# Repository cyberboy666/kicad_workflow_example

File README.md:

# kicad_workflow_example
an example kicad project to experiment with automated workflows

## goals

on every git _push_:
- check the schematic and pcb tester for problems (dont block just alert if there is something)

on every git _release_:
- run checkers...
- export schematic pdf
- export gerber files (lastest.zip format ?)
- export the bom's (full, tayda, mouser ibom)

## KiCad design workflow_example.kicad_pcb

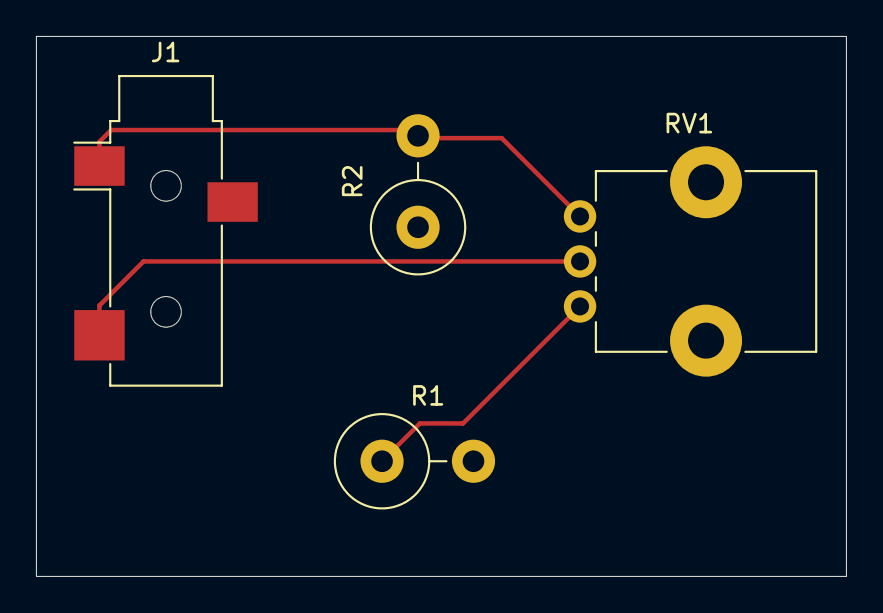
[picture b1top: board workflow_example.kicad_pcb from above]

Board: 2 copper layers, 45.0 x 30.0 mm, 4 parts (0 on the bottom side), 4 nets.

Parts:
J1: AudioJack2; Jack_3.5mm_CUI_SJ-3523-SMT_Horizontal
R1, R2: R; R_Axial_DIN0516_L15.5mm_D5.0mm_P5.08mm_Vertical
RV1: R_POT; Potentiometer_Alps_RK09K_Single_Vertical

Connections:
GND: J1.S, R2.1
unnamed: J1.T, RV1.2
unnamed: R1.1, RV1.1
unnamed: R2.2, RV1.3

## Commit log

2020-11-04 test commit
2020-11-04 change
2020-11-04 refolder
2020-11-04 add pcb
2020-11-04 example change
2020-11-04 update circuit
2020-11-04 Add changes
2020-11-04 broken schematic
2020-11-04 fix schematic
2020-11-04 some changes
2021-07-14 add bom generating script
